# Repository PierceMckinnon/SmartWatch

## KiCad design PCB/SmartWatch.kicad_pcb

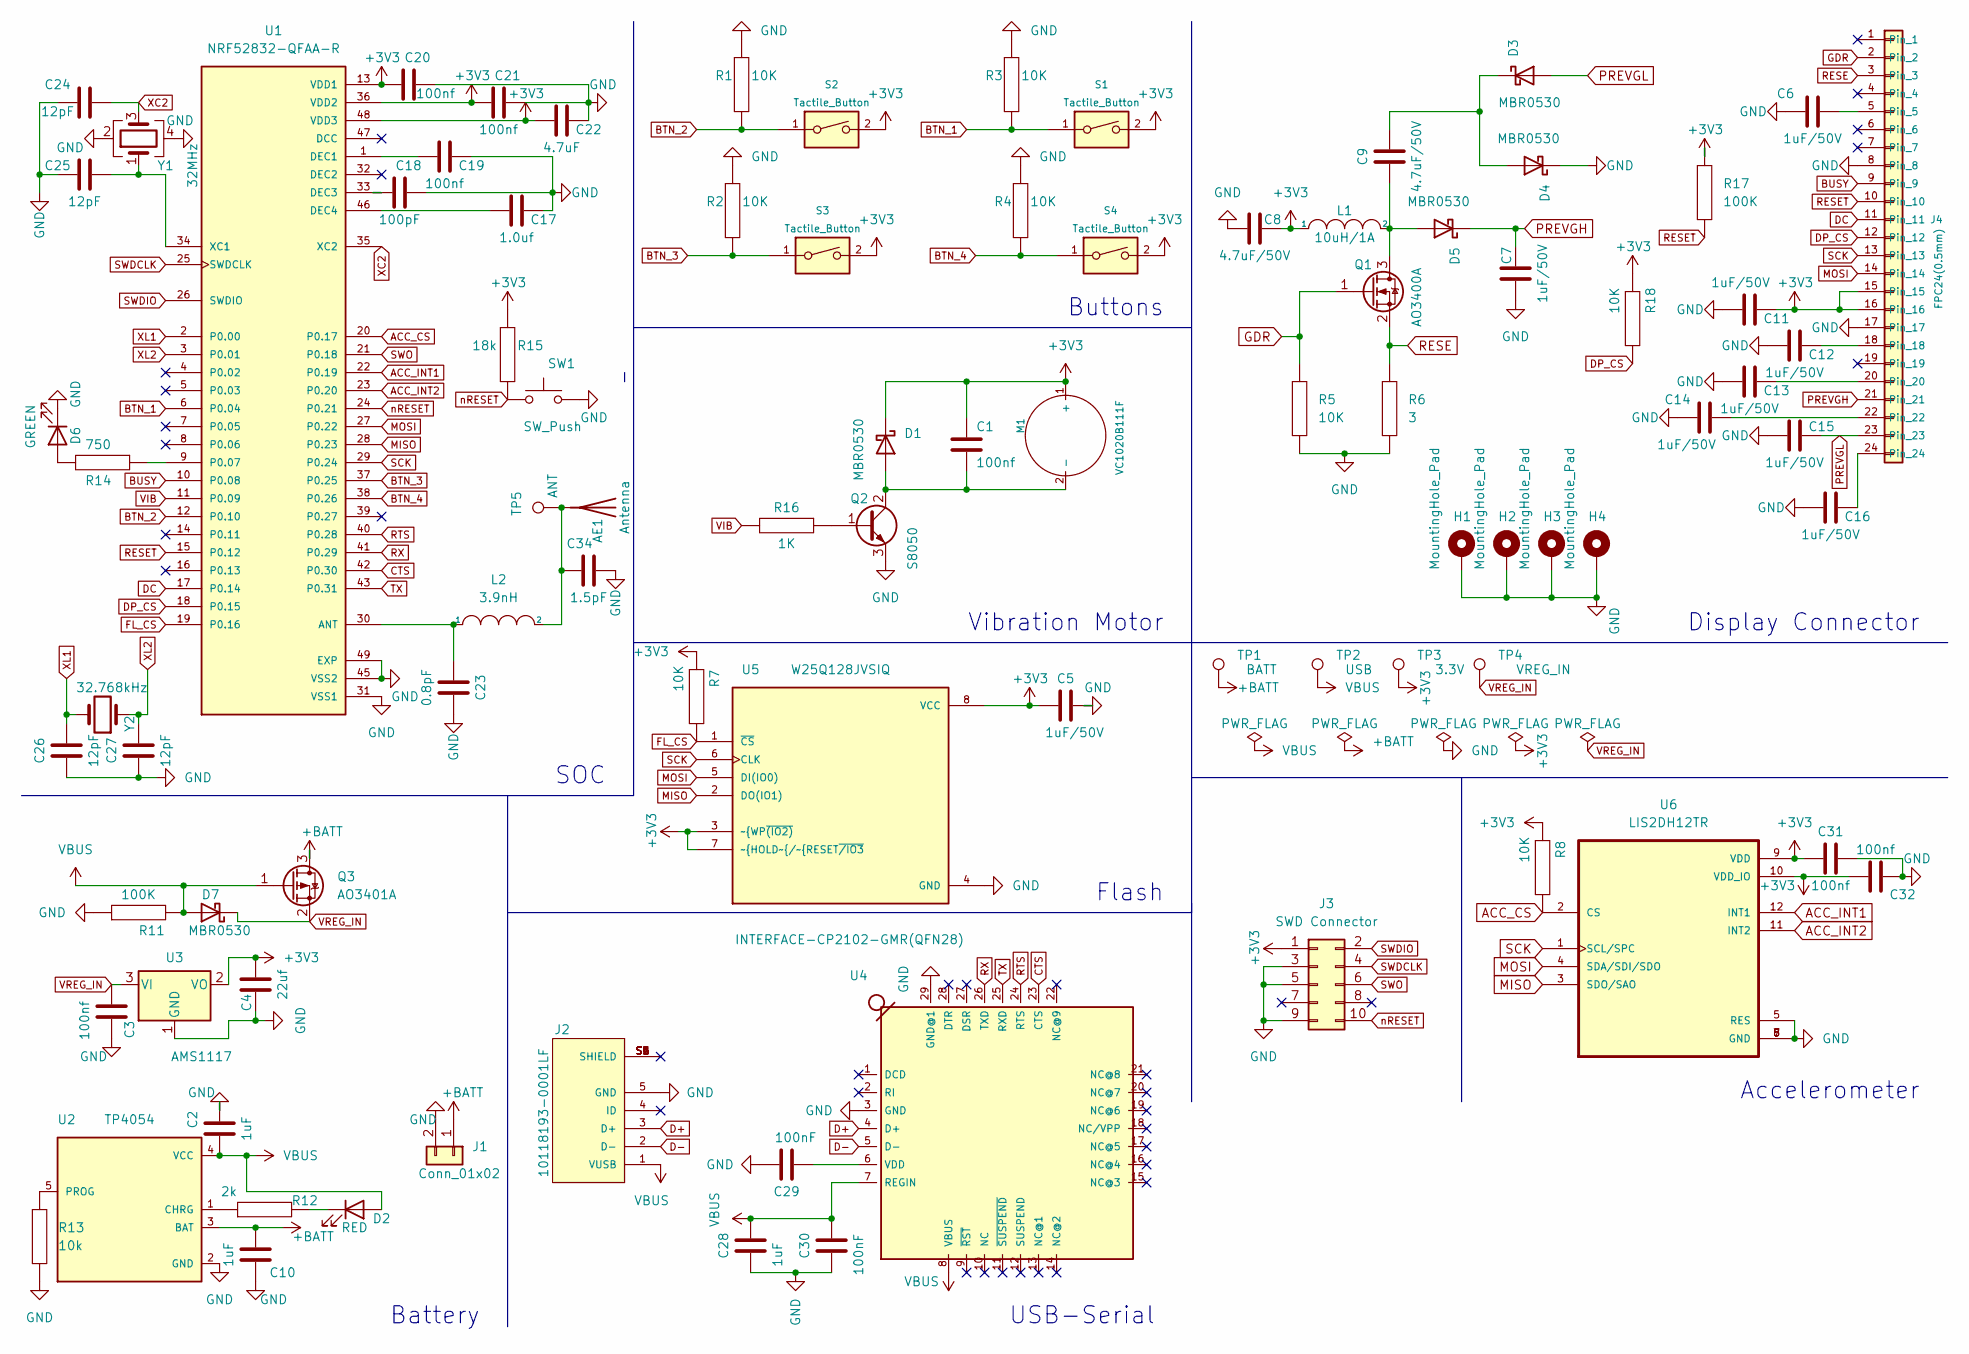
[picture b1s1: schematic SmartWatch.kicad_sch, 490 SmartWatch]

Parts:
AE1: Antenna
C1, C3: 100nf; C_0603_1608Metric
C2, C10, C28: 1uF; C_0603_1608Metric
C4: 22uf; C_0805_2012Metric
C5, C6, C7, C11, C12, C13, C14, C15, C16: 1uF/50V; C_0603_1608Metric
C8, C9: 4.7uF/50V; C_0805_2012Metric
C17: 1.0uf; C_0603_1608Metric
C18: 100pF; C_0402_1005Metric
C19, C20, C21, C31, C32: 100nf; C_0402_1005Metric
C22: 4.7uF; C_0603_1608Metric
C23: 0.8pF; C_0402_1005Metric
C24, C25, C26, C27: 12pF; C_0402_1005Metric
C29, C30: 100nF; C_0603_1608Metric
C34: 1.5pF; C_0402_1005Metric
D1, D3, D4, D5, D7: MBR0530; D_SOD-123
D2: RED; LED_0603_1608Metric
D6: GREEN; LED_0603_1608Metric
H1, H2, H3, H4: MountingHole_Pad; MountingHole_2.2mm_M2_Pad
J1: Conn_01x02; JST_PH_S2B-PH-K_1x02_P2.00mm_Horizontal
J2: 10118193-0001LF; FCI_10118193-0001LF
J3: SWD Connector; PinHeader_2x05_P2.54mm_Vertical
J4: FPC24(0.5mm); TE_2-1734839-4_1x24-1MP_P0.5mm_Horizontal
L1: 10uH/1A; L_0805_2012Metric
L2: 3.9nH; L_0402_1005Metric
M1: VC1020B111F; PinHeader_1x02_P1.27mm_Vertical
Q1: AO3400A; SOT-23
Q2: S8050; SOT-23
Q3: AO3401A; SOT-23
R1, R2, R3, R4, R5, R7, R8, R18: 10K; R_0402_1005Metric
R6: 3; R_0402_1005Metric
R11, R17: 100K; R_0402_1005Metric
R12: 2k; R_0402_1005Metric
R13: 10k; R_0402_1005Metric
R14: 750; R_0603_1608Metric
R15: 18k; R_0402_1005Metric
R16: 1K; R_0402_1005Metric
S1, S2, S3, S4: Tactile_Button; SW_SPST_EVQP7A
SW1: SW_Push; SW_SPST_PTS810
TP1: BATT; TestPoint_Pad_D1.0mm
TP2: USB; TestPoint_Pad_D1.0mm
TP3: 3.3V; TestPoint_Pad_D1.0mm
TP4: VREG_IN; TestPoint_Pad_D1.0mm
TP5: ANT; TestPoint_Pad_D1.0mm
U1: NRF52832-QFAA-R; QFN-48-1EP_6x6mm_P0.4mm_EP4.6x4.6mm
U2: TP4054; SOT-23-5; PARTREV 1
U3: AMS1117; SOT-223
U4: INTERFACE-CP2102-GMR(QFN28); QFN28G_0.5-5X5MM; MPN CP2102-GMR
U5: W25Q128JVSIQ; SOIC-8_5.275x5.275mm_P1.27mm; PARTREV C
U6: LIS2DH12TR; LGA-12_2x2mm_P0.5mm
Y1: 32MHz; Crystal_SMD_2016-4Pin_2.0x1.6mm
Y2: 32.768kHz; Crystal_SMD_3215-2Pin_3.2x1.5mm

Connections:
+3V3: C1.1, C4.2, C5.1, C8.1, C11.1, C20.2, C21.2, C22.2, C31.1, C32.1, D1.1 (K), J3.1, J4.15, J4.16, L1.1, M1.1 (+), R7.1, R8.1, R15.1, R17.1, R18.1, S1.2, S2.2, S3.2, S4.2, TP3.1, U1.13 (VDD1), U1.36 (VDD2), U1.48 (VDD3), U3.2 (VO), U5.3 (~WP~{(IO2)), U5.7 (~HOLD~{/~{RESET~{/IO3), U5.8 (VCC), U6.9 (VDD), U6.10 (VDD_IO)
+BATT: C10.2, J1.1, Q3.3 (D), TP1.1, U2.3 (BAT)
ACC_CS: R8.2, U1.20 (P0.17), U6.2 (CS)
ACC_INT1: U1.22 (P0.19), U6.12 (INT1)
ACC_INT2: U1.23 (P0.20), U6.11 (INT2)
BTN_1: R3.2, S1.1, U1.6 (P0.04)
BTN_2: R1.2, S2.1, U1.12 (P0.10)
BTN_3: R2.2, S3.1, U1.37 (P0.25)
BTN_4: R4.2, S4.1, U1.38 (P0.26)
BUSY: J4.9, U1.10 (P0.08)
CTS: U1.42 (P0.30), U4.23 (CTS)
D+: J2.3 (D+), U4.4 (D+)
D-: J2.2 (D-), U4.5 (D-)
DC: J4.11, U1.17 (P0.14)
DP_CS: J4.12, R18.2, U1.18 (P0.15)
FL_CS: R7.2, U1.19 (P0.16), U5.1 (~CS)
GDR: J4.2, Q1.1 (G), R5.1
GND: C2.2, C3.1, C4.1, C5.2, C6.2, C7.2, C8.2, C10.1, C11.2, C12.2, C13.2, C14.2, C15.2, C16.2, C17.1, C18.1, C19.1, C20.1, C21.1, C22.1, C23.1, C24.2, C25.2, C26.2, C27.2, C28.2, C29.1, C30.2, C31.2, C32.2, C34.1, D4.1 (K), D6.1 (K), H1.1, H2.1, H3.1, H4.1, J1.2, J2.5 (GND), J3.3, J3.5, J3.9, J4.8, J4.17, Q2.3 (E), R1.1, R2.1, R3.1, R4.1, R5.2, R6.2, R11.1, R13.2, SW1.2, U1.31 (VSS1), U1.45 (VSS2), U1.49 (EXP), U2.2 (GND), U3.1 (GND), U4.3 (GND), U4.29 (GND@1), U5.4 (GND), U6.5 (RES), U6.6 (GND), U6.7 (GND), U6.8 (GND), Y1.2, Y1.4
MISO: U1.28 (P0.23), U5.2 (DO(IO1)), U6.3 (SDO/SAO)
MOSI: J4.14, U1.27 (P0.22), U5.5 (DI(IO0)), U6.4 (SDA/SDI/SDO)
unnamed: C1.2, D1.2 (A), M1.2 (-), Q2.2 (C)
unnamed: C6.1, J4.5
unnamed: C9.1, D3.1 (K), D4.2 (A)
unnamed: C9.2, D5.2 (A), L1.2, Q1.3 (D)
unnamed: C12.1, J4.18
unnamed: C13.1, J4.20
unnamed: C14.1, J4.22
unnamed: C16.1, J4.24
unnamed: C17.2, U1.46 (DEC4)
unnamed: C18.2, U1.33 (DEC3)
unnamed: C19.2, U1.1 (DEC1)
unnamed: C23.2, L2.1, U1.30 (ANT)
unnamed: C25.1, U1.34 (XC1), Y1.1
unnamed: C29.2, U4.6 (VDD)
unnamed: D2.1 (K), R12.2
unnamed: D6.2 (A), R14.2
unnamed: AE1.1 (A), C34.2, L2.2, TP5.1
unnamed: Q2.1 (B), R16.1
unnamed: R12.1, U2.1 (CHRG)
unnamed: R13.1, U2.5 (PROG)
unnamed: R14.1, U1.9 (P0.07)
PREVGH: C7.1, D5.1 (K), J4.21
PREVGL: C15.1, D3.2 (A), J4.23
RESE: J4.3, Q1.2 (S), R6.1
RESET: J4.10, R17.2, U1.15 (P0.12)
RTS: U1.40 (P0.28), U4.24 (RTS)
RX: U1.41 (P0.29), U4.26 (TXD)
SCK: J4.13, U1.29 (P0.24), U5.6 (CLK), U6.1 (SCL/SPC)
SWDCLK: J3.4, U1.25 (SWDCLK)
SWDIO: J3.2, U1.26 (SWDIO)
SWO: J3.6, U1.21 (P0.18)
TX: U1.43 (P0.31), U4.25 (RXD)
VBUS: C2.1, C28.1, C30.1, D2.2 (A), D7.2 (A), J2.1 (VUSB), Q3.1 (G), R11.2, TP2.1, U2.4 (VCC), U4.7 (REGIN), U4.8 (VBUS)
VIB: R16.2, U1.11 (P0.09)
VREG_IN: C3.2, D7.1 (K), Q3.2 (S), TP4.1, U3.3 (VI)
XC2: C24.1, U1.35 (XC2), Y1.3
XL1: C26.1, U1.2 (P0.00), Y2.2
XL2: C27.1, U1.3 (P0.01), Y2.1
nRESET: J3.10, R15.2, SW1.1, U1.24 (P0.21)

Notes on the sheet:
Accelerometer
Vibration Motor
Flash
USB-Serial
SOC
Buttons
Display Connector
Battery

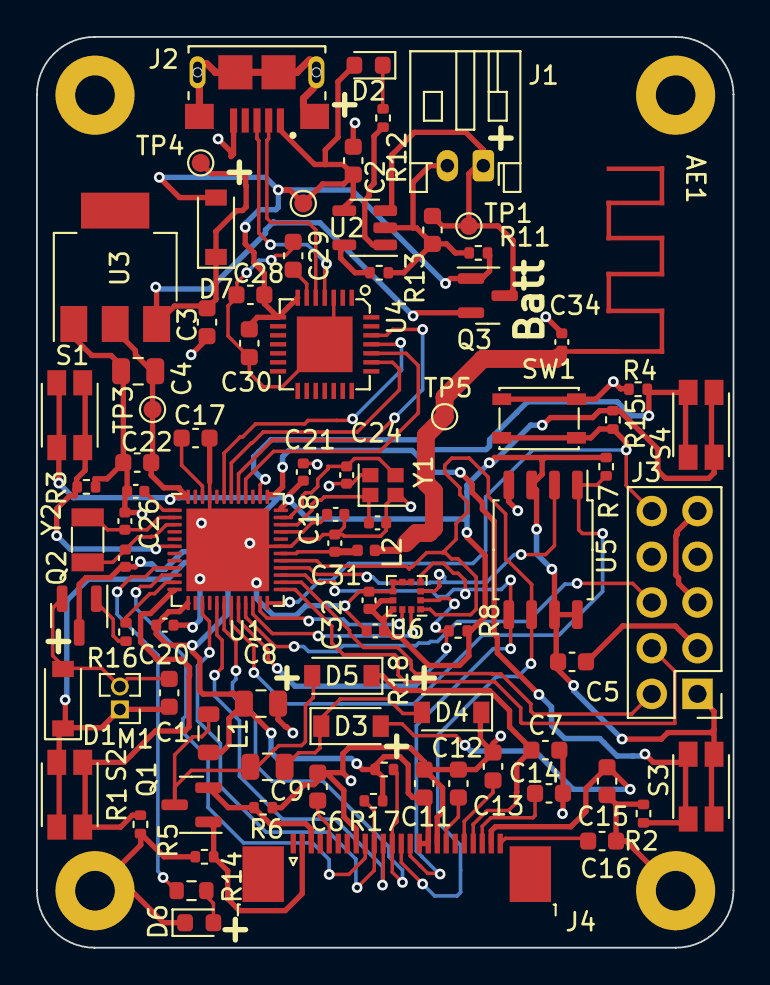
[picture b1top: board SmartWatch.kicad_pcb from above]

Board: 2 copper layers, 38.7 x 50.6 mm, 89 parts (0 on the bottom side), 59 nets.

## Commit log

2022-11-17 Toolchain HowTo
2022-11-17 Revert "first commit"
    This reverts commit 5e2a5efef8af36b434600cf299acb26ec635f76c.
2022-11-19 Blinky LED minimalist example
2022-11-19 Template
2022-11-19 Add recover to makefile
2022-11-19 Update howto with compiling/running info
2023-02-24 Working barebones gfx
2023-02-24 -Add FreeRTOS -Working GFX Example
2023-03-12 Add Features: -Clock/Calendar -Homescreen Navigation -All button ints -RTC ints -Sleep timer -Non rtc blocking delay after display
2023-03-14 Change pin config for PCB
2023-03-14 Add pin config file to make chaning pins easier
2023-03-15 Fix button double int: -Fix pin config for dev kit -Add int delay after button click -Increase int prio for rtc so unninterupteable
2023-03-20 Added Features: -Fixed GPIO Pin 10 nfc bug -Added Flash Driver(untested) -Added barebones file uart -Change to single SPI driver
2023-03-23 Working text files
2023-03-23 Music Working... I think
2023-03-23 Add vibration on upload event
2023-04-19 Add HW files
